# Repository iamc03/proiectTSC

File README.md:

# Proiect TSC
 ## Diagrama Bloc

 ## Bill of Materials
 | Component       | Datasheet       | Link           |
 |-----------------|-----------------|----------------|
 | ESP32-C6-WROOM-1-N8 | - | https://www.snapeda.com/parts/ESP32-C6-WROOM-1-N8/Espressif+Systems/view-part/?ref=eda |
 | CPH3225A | - | https://www.snapeda.com/parts/CPH3225A/Seiko+Instruments/view-part/?ref=eda |
 | DS3231SN# | - | https://www.snapeda.com/parts/DS3231SN%23/Analog+Devices/view-part/?ref=eda |
 | MAX17048G+T10 | - | https://www.snapeda.com/parts/MAX17048G+T10/Analog+Devices/view-part/?ref=eda|
 | MBR0530 | - | https://www.snapeda.com/parts/MBR0530/Onsemi/view-part/?ref=eda |
 | PGB1010603MR | - | https://www.snapeda.com/parts/PGB1010603MR/Littelfuse/view-part/?ref=eda |
 | USBLC6-2SC6Y | - | https://www.snapeda.com/parts/USBLC6-2SC6Y/STMicroelectronics/view-part/?ref=eda |
 | W25Q512JVEIQ | - | https://www.snapeda.com/parts/W25Q512JVEIQ/Winbond+Electronics/view-part/?ref=eda |
 | 640-USB4110-GF-A | - | https://www.mouser.co.uk/ProductDetail/GCT/USB4110-GF-A?qs=KUoIvG%2F9IlYiZvIXQjyJeA%3D%3D |
 | PGB1010603MR | - | https://www.snapeda.com/parts/PGB1010603MR/Littelfuse/view-part/?ref=snap |
 | BUTTONS | - | https://industry.panasonic.com/global/en/products/control/switch/light-touch/number/evqpuj02k |
 | C (1-10) | - | https://componentsearchengine.com/part-view/CC0402MRX5R5BB106/YAGEO |
 | LED | - | https://www.snapeda.com/parts/KP-1608SURCK/Kingbright/view-part/?ref=search&t=LED%200603 |
 | D (1-12) | - | https://www.snapeda.com/parts/PGB1010603MR/Littelfuse/view-part/?ref=eda |
 | R (1-15) | - | https://componentsearchengine.com/part-view/R0402%201%25%20100%20K%20(RC0402FR-07100KL)/YAGEO |
 | Test Pads | - | - |
   
## Funcționalitate hardware
### Alimentare și încărcare
Conector USB + MCP73831: Permite încărcarea unei baterii LiPo prin USB.

LDO (ME6211 sau similar): Reglează tensiunea la 3.3V pentru alimentarea circuitului digital.

Condensatori de decuplare: Plasați strategic pentru stabilizarea alimentării.

### ESP32-C6
Modul WiFi/BLE cu capabilități de conectare și procesare date.

Flash: 4MB / RAM: 512KB.

GPIO multiple folosite pentru comunicații (SPI, I2C) și control periferice.

### E-Ink Display
Controlat prin SPI.

GPIO-uri adiționale pentru semnale de control (busy, reset).

### Protecții
Diodă Schottky (ex: MBR0530) pentru protecție polaritate inversă.

PTC resetabil pentru protecție curent.

### EEPROM / MEMS
EEPROM pentru păstrarea datelor între cicluri de alimentare (presupus U3).

MAX17048 pentru monitorizarea nivelului bateriei (comunicare I2C).

| Pin ESP32-C6 |	Funcție hardware |
|-------------|------------------|
| IO0 |	GPIO / Boot	|
| IO1 |	UART TX |
| IO2 |	UART RX	|
| IO3 |	GPIO	|
| IO4 | GPIO	|
| IO5 |	GPIO	|
| IO6 |	GPIO	|
| IO7 |	GPIO	|
| IO8 |	GPIO	|
| IO9 |	SPI Flash – IO2 |
| IO10 | 	SPI Flash – IO3 |
| IO11 |	SPI Flash – SCK |
| IO12 |	SPI Flash – CS |
| IO13 |	SPI Flash – IO1 |
| IO14 |	SPI Flash – IO0 |
| IO15 |	I2C SDA |
| IO16 |	I2C SCL |
| IO17 |	SPI Display – DC |
| IO18 |	SPI Display – RST |
| IO19 |	SPI Display – CS |
| IO20 |	SPI Display – CLK |
| IO21 |	SPI Display – MOSI |
| IO22 |	SPI Display – BUSY |
| IO23 |	SPI ESD / Qwiic |

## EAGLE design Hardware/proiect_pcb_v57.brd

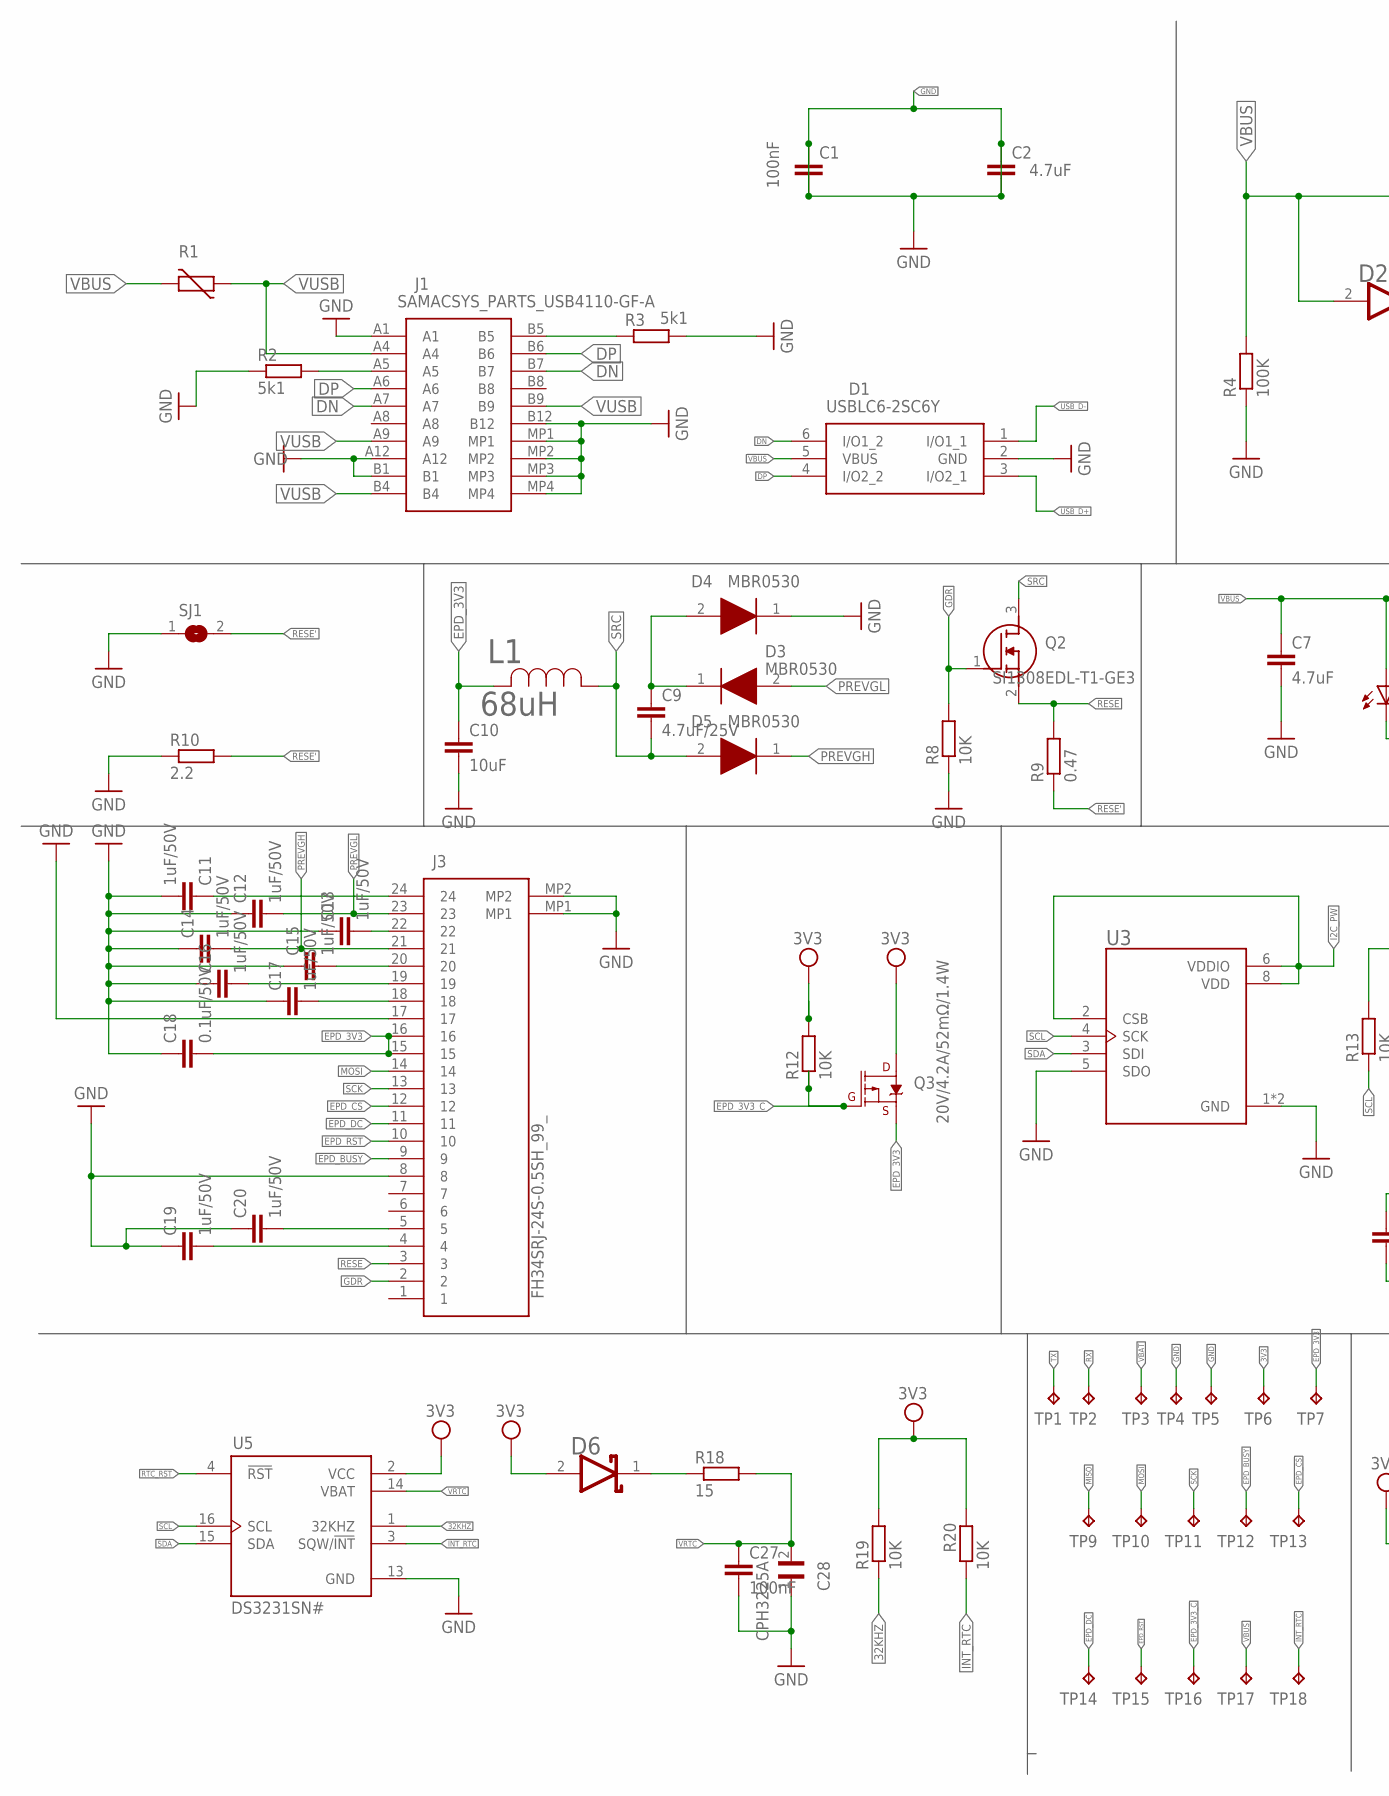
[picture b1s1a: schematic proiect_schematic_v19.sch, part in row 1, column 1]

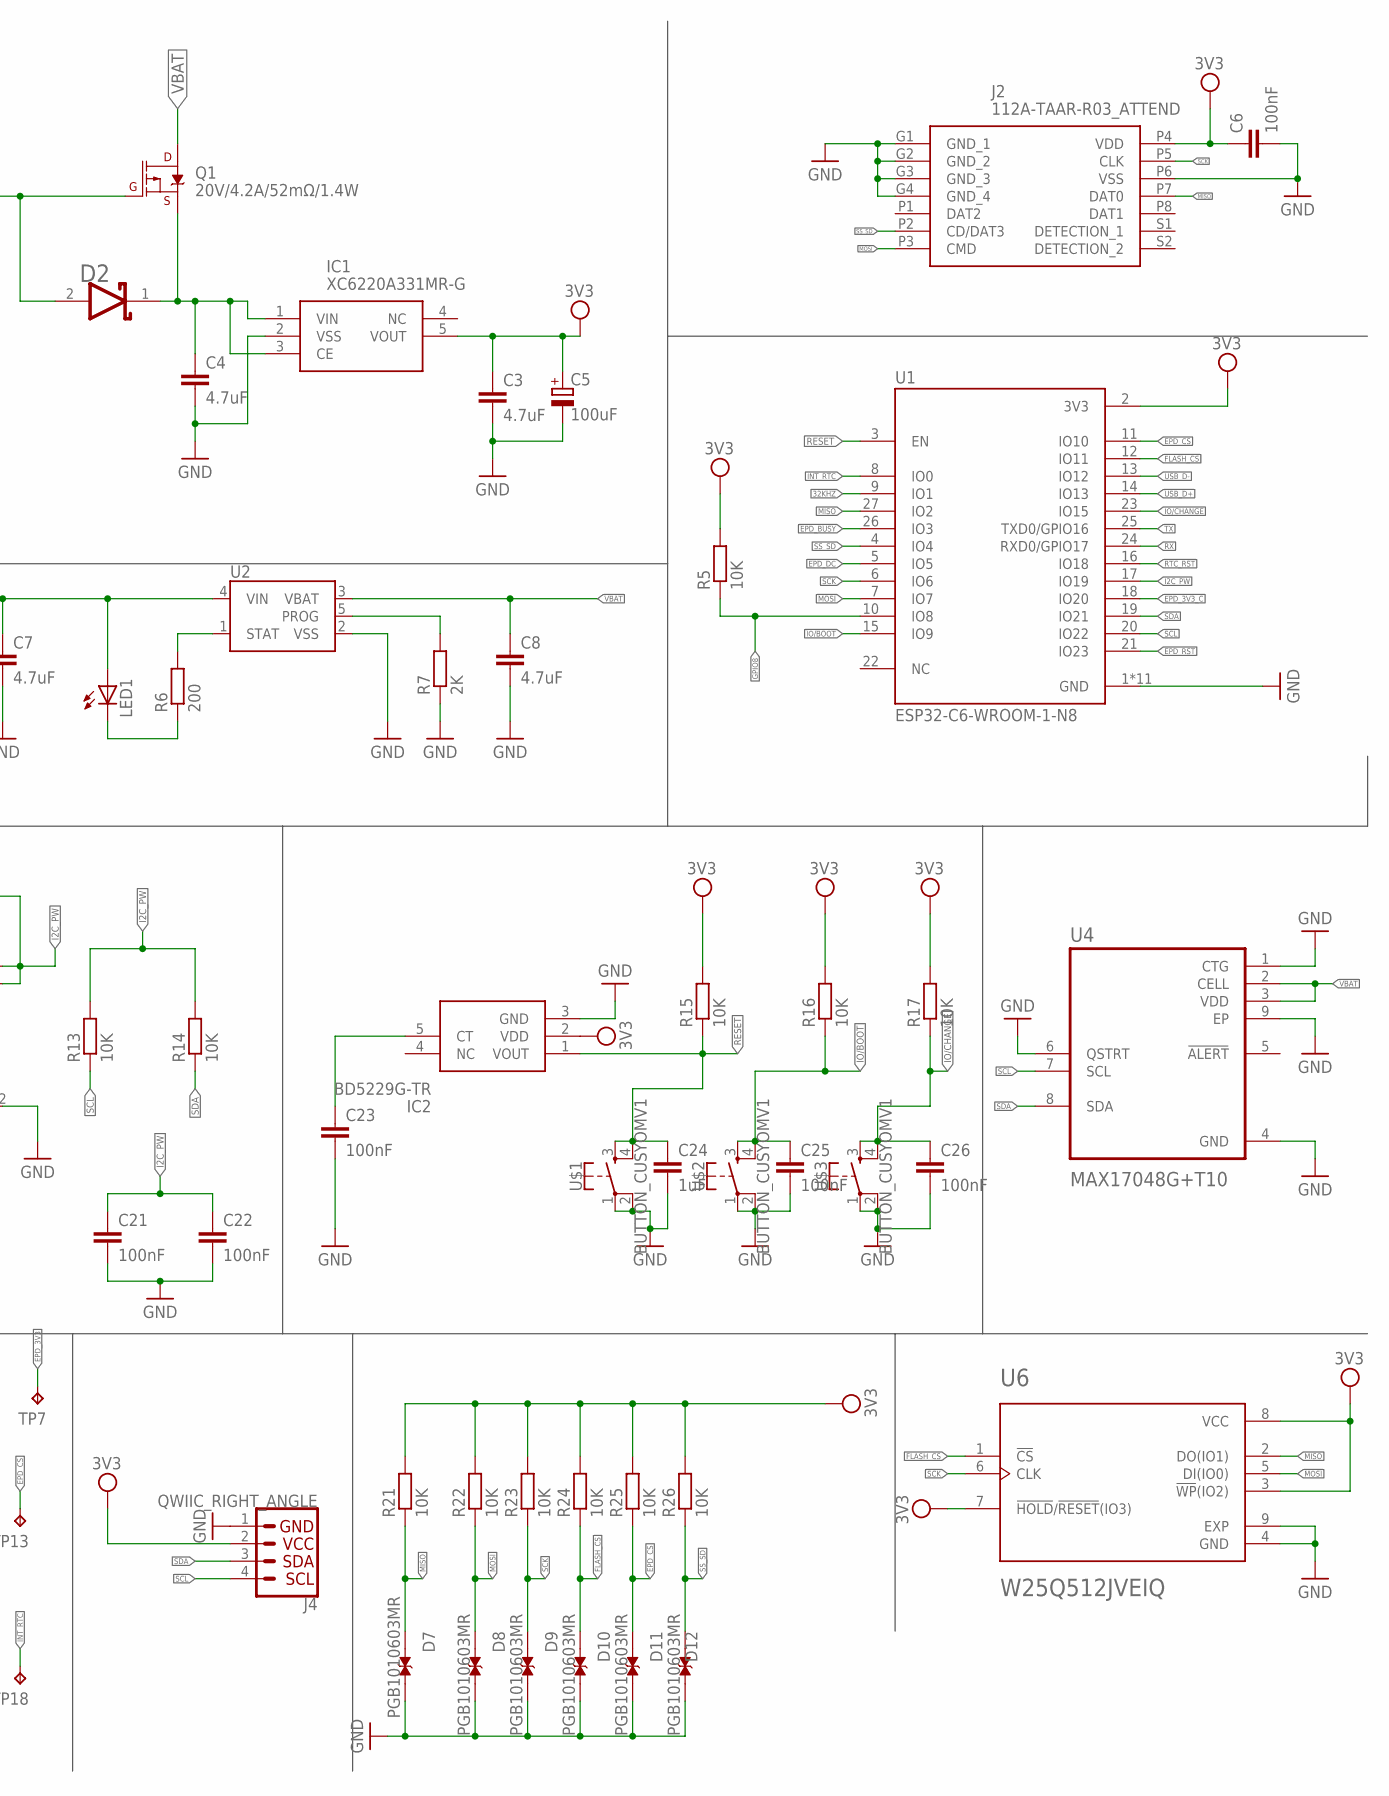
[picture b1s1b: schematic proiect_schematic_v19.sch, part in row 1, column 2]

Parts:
C1, C6, C21, C22, C23, C25, C26, C27: 100nF; ESP32_WROVER_EAGLE-LTSPICE_C0402
C2, C7, C8: 4.7uF; ESP32_WROVER_EAGLE-LTSPICE_C0402
C3, C4: 4.7uF; EAGLE-LTSPICE_C0402
C5: 100uF; RCL_CT3528
C9: 4.7uF/25V; ESP32_WROVER_EAGLE-LTSPICE_C0402
C10: 10uF; ESP32_WROVER_EAGLE-LTSPICE_C0402
C11, C12, C13, C14, C15, C16, C17, C19, C20: 1uF/50V; ESP32_WROVER_EAGLE-LTSPICE_C0402
C18: 0.1uF/50V; ESP32_WROVER_EAGLE-LTSPICE_C0402
C24: 1uF; ESP32_WROVER_EAGLE-LTSPICE_C0402
C28: CPH3225A; CAPCP3225X100N
D1: USBLC6-2SC6Y; SOT95P280X145-6N
D2, D6: ESP32_WROVER_AVX---SD0805S020S1R0_AVX_SD0805S020S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; ESP32_WROVER_AVX---SD0805S020S1R0_AVX_SD0805S020S1R0_0
D3, D4, D5: MBR0530; SOD3716X135N
D7, D8, D9, D10, D11, D12: PGB1010603MR; DIOC1608X36N
IC1: XC6220A331MR-G; SOT95P280X120-5N
IC2: BD5229G-TR; SOT95P280X125-5N
J1: SAMACSYS_PARTS_USB4110-GF-A; SAMACSYS_PARTS_USB4110GFA
J2: 112A-TAAR-R03_ATTEND; 112ATAARR03ATTEND
J3: FH34SRJ-24S-0.5SH_99_; FH34SRJ24S05SH99
J4: QWIIC_RIGHT_ANGLE; JST04_1MM_RA
L1: 68uH; IND_4828-WE-TPC_WRE
LED1: ADAFRUIT_LEDCHIP-LED0603; ADAFRUIT_CHIP-LED0603
Q1, Q3: 20V/4.2A/52mΩ/1.4W; ESP32_WROVER_SPARKFUN-DISCRETESEMI_SOT23-3
Q2: SI1308EDL-T1-GE3; SOT65P210X110-3N
R1: ESP32C6_VARISTORCN1812; ESP32C6_VARISTOR_CT/CN1812
R2, R3: 5k1; ESP32_WROVER_EAGLE-LTSPICE_R0402
R4: 100K; ESP32_WROVER_EAGLE-LTSPICE_R0402
R5, R8, R12, R13, R14, R15, R16, R17, R19, R20, R21, R22, R23, R24, R25, R26: 10K; ESP32_WROVER_EAGLE-LTSPICE_R0402
R6: 200; ESP32_WROVER_EAGLE-LTSPICE_R0402
R7: 2K; ESP32_WROVER_EAGLE-LTSPICE_R0402
R9: 0.47; ESP32_WROVER_EAGLE-LTSPICE_R0402
R10: 2.2; ESP32_WROVER_EAGLE-LTSPICE_R0402
R18: 15; ESP32_WROVER_EAGLE-LTSPICE_R0402
SJ1: SJ
TP1, TP2, TP3, TP4, TP5, TP6, TP7, TP9, TP10, TP11, TP12, TP13, TP14, TP15, TP16, TP17, TP18: TPTP20R; TP20R
U1: ESP32-C6-WROOM-1-N8; XCVR_ESP32-C6-WROOM-1-N8
U2: ESP32_WROVER_SPARKFUN-IC-POWER_MCP73831; ESP32_WROVER_SPARKFUN-IC-POWER_SOT23-5
U3: ESP32_WROVER_BME680_BME680; ESP32_WROVER_BME680_PSON80P300X300X100-8N
U4: MAX17048G+T10; SON50P200X200X80-9N
U5: DS3231SN#; SOIC127P1032X265-16N
U6: W25Q512JVEIQ; SON127P600X800X80-9N
U$1, U$2, U$3: BUTTON_CUSYOMV1; MYBUTTON

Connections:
3V3: C3.1, C5.+, C6.1, D6.2 (ANODE), IC1.5 (VOUT), IC2.2 (VDD), J2.P4 (VDD), J4.2, Q3.3 (D), R5.2, R12.2, R15.2, R16.2, R17.2, R19.2, R20.2, R21.2, R22.2, R23.2, R24.2, R25.2, R26.2, TP6.TP, U1.2 (3V3), U5.2 (VCC), U6.3 (!WP!(IO2)), U6.7 (!HOLD!/!RESET!(IO3)), U6.8 (VCC)
32KHZ: R19.1, U1.9 (IO1), U5.1 (32KHZ)
DN: D1.6 (I/O1_2), J1.A7, J1.B7
DP: D1.4 (I/O2_2), J1.A6, J1.B6
EPD_3V3: C10.1, C18.2, J3.15, J3.16, L1.2, Q3.2 (S), TP7.TP
EPD_3V3_C: Q3.1 (G), R12.1, TP16.TP, U1.18 (IO20)
EPD_BUSY: J3.9, TP12.TP, U1.26 (IO3)
EPD_CS: D11.1, J3.12, R25.1, TP13.TP, U1.11 (IO10)
EPD_DC: J3.11, TP14.TP, U1.5 (IO5)
EPD_RST: J3.10, TP15.TP, U1.21 (IO23)
FLASH_CS: D10.1, R24.1, U1.12 (IO11), U6.1 (!CS)
GDR: J3.2, Q2.1 (G), R8.2
GND: C1.1, C1.2, C2.1, C2.2, C3.2, C4.2, C5.-, C6.2, C7.2, C8.2, C10.2, C11.2, C12.1, C13.1, C14.1, C15.1, C16.1, C17.1, C18.1, C19.1, C20.1, C21.2, C22.2, C23.2, C24.2, C25.2, C26.2, C27.2, C28.1, D1.2 (GND), D4.1 (K), D7.2, D8.2, D9.2, D10.2, D11.2, D12.2, IC1.2 (VSS), IC2.3 (GND), J1.A1, J1.A12, J1.B1, J1.B12, J1.MP1, J1.MP2, J1.MP3, J1.MP4, J2.G1 (GND_1), J2.G2 (GND_2), J2.G3 (GND_3), J2.G4 (GND_4), J2.P6 (VSS), J3.8, J3.17, J3.MP1, J3.MP2, J4.1, R2.1, R3.2, R4.1, R7.1, R8.1, R10.1, SJ1.1, TP4.TP, TP5.TP, U1.1 (GND), U1.28 (GND), U1.29_1 (GND), U1.29_2 (GND), U1.29_3 (GND), U1.29_4 (GND), U1.29_5 (GND), U1.29_6 (GND), U1.29_7 (GND), U1.29_8 (GND), U1.29_9 (GND), U2.2 (VSS), U3.1 (GND), U3.5 (SDO), U3.7 (GND), U4.1 (CTG), U4.4 (GND), U4.6 (QSTRT), U4.9 (EP), U5.13 (GND), U6.4 (GND), U6.9 (EXP), U$1.1, U$1.2, U$2.1, U$2.2, U$3.1, U$3.2
GPIO8: R5.1, U1.10 (IO8)
I2C_PW: C21.1, C22.1, R13.2, R14.2, U1.17 (IO19), U3.2 (CSB), U3.6 (VDDIO), U3.8 (VDD)
INT_RTC: R20.1, TP18.TP, U1.8 (IO0), U5.3 (SQW/!INT)
IO/BOOT: C25.1, R16.1, U1.15 (IO9), U$2.3, U$2.4
IO/CHANGE: C26.1, R17.1, U1.23 (IO15), U$3.3, U$3.4
MISO: D7.1, J2.P7 (DAT0), R21.1, TP9.TP, U1.27 (IO2), U6.2 (DO(IO1))
MOSI: D8.1, J2.P3 (CMD), J3.14, R22.1, TP10.TP, U1.7 (IO7), U6.5 (DI(IO0))
unnamed: J1.A5, R2.2
unnamed: J1.B5, R3.1
unnamed: C11.1, J3.24
unnamed: C4.1, D2.1 (CATHODE), IC1.1 (VIN), IC1.3 (CE), Q1.2 (S)
unnamed: R6.2, U2.1 (STAT)
unnamed: LED1.C, R6.1
unnamed: R7.2, U2.5 (PROG)
unnamed: C9.1, D3.1 (K), D4.2 (A)
unnamed: C13.2, J3.22
unnamed: C15.2, J3.20
unnamed: C16.2, J3.19
unnamed: C17.2, J3.18
unnamed: C19.2, J3.4
unnamed: C20.2, J3.5
unnamed: C23.1, IC2.5 (CT)
unnamed: D6.1 (CATHODE), R18.1
PREVGH: C14.2, D5.1 (K), J3.21
PREVGL: C12.2, D3.2 (A), J3.23
RESE: J3.3, Q2.2 (S), R9.2
RESE': R9.1, R10.2, SJ1.2
RESET: C24.1, IC2.1 (VOUT), R15.1, U1.3 (EN), U$1.3, U$1.4
RTC_RST: U1.16 (IO18), U5.4 (!RST)
RX: TP2.TP, U1.24 (RXD0/GPIO17)
SCK: D9.1, J2.P5 (CLK), J3.13, R23.1, TP11.TP, U1.6 (IO6), U6.6 (CLK)
SCL: J4.4, R13.1, U1.20 (IO22), U3.4 (SCK), U4.7 (SCL), U5.16 (SCL)
SDA: J4.3, R14.1, U1.19 (IO21), U3.3 (SDI), U4.8 (SDA), U5.15 (SDA)
SRC: C9.2, D5.2 (A), L1.1, Q2.3 (D)
SS_SD: D12.1, J2.P2 (CD/DAT3), R26.1, U1.4 (IO4)
TX: TP1.TP, U1.25 (TXD0/GPIO16)
USB_D+: D1.3 (I/O2_1), U1.14 (IO13)
USB_D-: D1.1 (I/O1_1), U1.13 (IO12)
VBAT: C8.1, Q1.3 (D), TP3.TP, U2.3 (VBAT), U4.2 (CELL), U4.3 (VDD)
VBUS: C7.1, D1.5 (VBUS), D2.2 (ANODE), LED1.A, Q1.1 (G), R1.2, R4.2, TP17.TP, U2.4 (VIN)
VRTC: C27.1, C28.2, R18.2, U5.14 (VBAT)
VUSB: J1.A4, J1.A9, J1.B4, J1.B9, R1.1

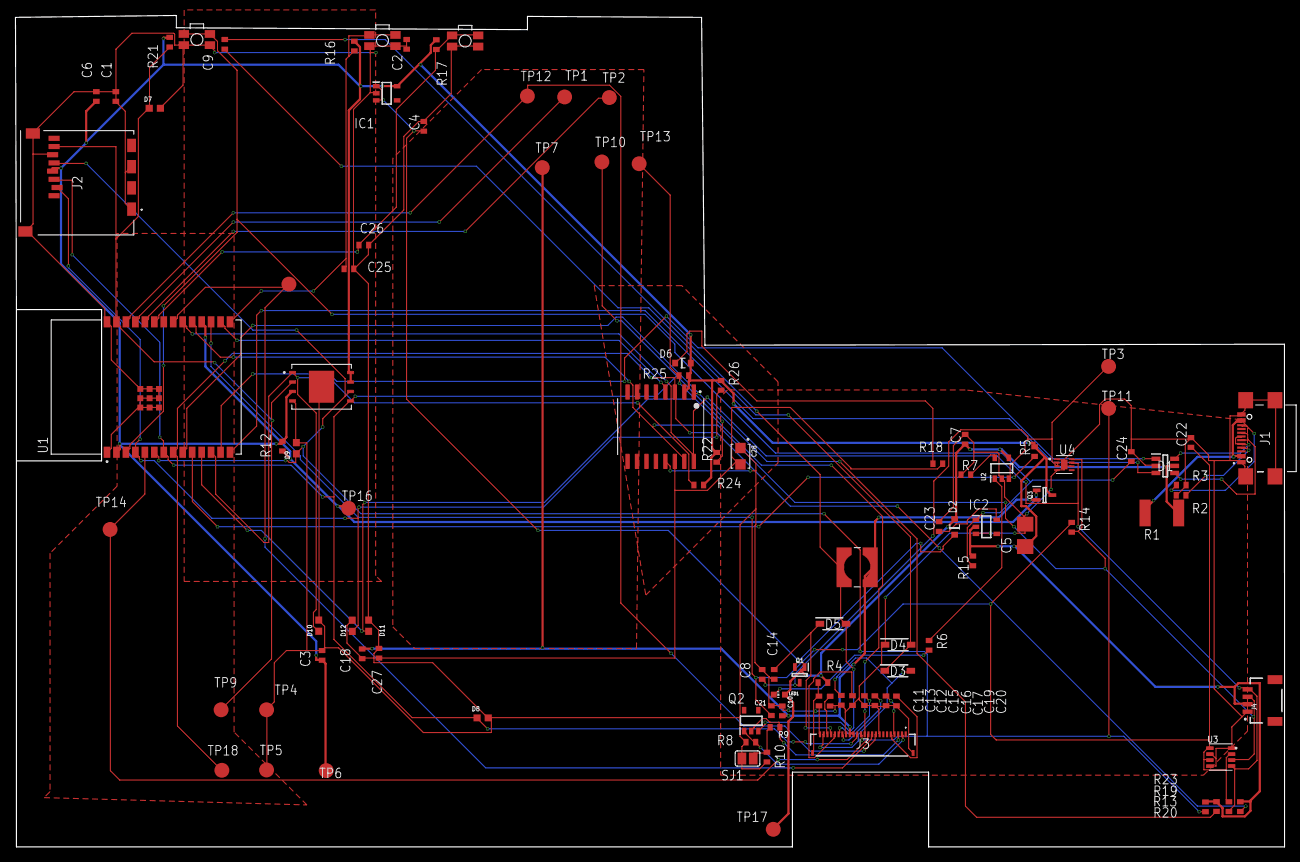
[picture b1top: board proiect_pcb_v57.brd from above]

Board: 2 copper layers, 170.3 x 111.6 mm, 103 parts (0 on the bottom side), 55 nets.

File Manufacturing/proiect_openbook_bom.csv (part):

Qty,Value,Device,Package,Parts,Description,ARROW_PART_NUMBER,ARROW_PRICE-STOCK,AVAILABILITY,CENTROID_NOT_SPECIFIED,CHECK_PRICES,COPYRIGHT,DATASHEET,DESCRIPTION,DIGIKEY_DESCRIPTION,DIGIKEY_PART_NUMBER,HEIGHT,LEAD_FREE,MANUFACTURER_NAME,MANUFACTURER_PART_NUMBER,MF,MFR_NAME,MOUSER_PART_NUMBER,MOUSER_PRICE-STOCK,MOUSER_TESTING_PART_NUMBER,MOUSER_TESTING_PRICE-STOCK,MP,MPN,PACKAGE,POPULARITY,PREFIX,PRICE,PROD_ID,PURCHASE-URL,ROHS,SNAPEDA_LINK,SPICEMODEL,SPICEPREFIX,TEMPERATURE_RANGE_HIGH,TEMPERATURE_RANGE_LOW,TP_SIGNAL_NAME,VALUE
1,,ADAFRUIT_LEDCHIP-LED0603,ADAFRUIT_CHIP-LED0603,LED1,LED,,,,,,,,,,,,,,,,,,,,,,,,,,,,,,,,,,,,
1,,SJ,SJ,SJ1,"SMD solder JUMPER",,,,,,,,,,,,,,,,,,,,,,,,3,,,,,,,,,,,,
1,0.1uF/50V,ESP32_WROVER_EAGLE-LTSPICE_CC0402,ESP32_WROVER_EAGLE-LTSPICE_C0402,C18,"CAPACITOR, European symbol",,,,,,,,,,,,,,,,,,,,,,,,,,,,,,,NONE,C,,,,
1,0.47,ESP32_WROVER_EAGLE-LTSPICE_RR0402,ESP32_WROVER_EAGLE-LTSPICE_R0402,R9,"RESISTOR, European symbol",,,,,,,,,,,,,,,,,,,,,,,,,,,,,,,NONE,R,,,,
1,100K,ESP32_WROVER_EAGLE-LTSPICE_RR0402,ESP32_WROVER_EAGLE-LTSPICE_R0402,R4,"RESISTOR, European symbol",,,,,,,,,,,,,,,,,,,,,,,,,,,,,,,NONE,R,,,,
8,100nF,ESP32_WROVER_EAGLE-LTSPICE_CC0402,ESP32_WROVER_EAGLE-LTSPICE_C0402,"C1, C6, C21, C22, C23, C25, C26, C27","CAPACITOR, European symbol",,,,,,,,,,,,,,,,,,,,,,,,,,,,,,,NONE,C,,,,
1,100uF,RCL_CPOL-EUCT3528,RCL_CT3528,C5,"POLARIZED CAPACITOR, European symbol",,,,,,,,,,,,,,,,,,,,,,,,0,,,,,,,,C,,,,
16,10K,ESP32_WROVER_EAGLE-LTSPICE_RR0402,ESP32_WROVER_EAGLE-LTSPICE_R0402,"R5, R8, R12, R13, R14, R15, R16, R17, R19, R20, R21, R22, R23, R24, R25, R26","RESISTOR, European symbol",,,,,,,,,,,,,,,,,,,,,,,,,,,,,,,NONE,R,,,,
1,10uF,ESP32_WROVER_EAGLE-LTSPICE_CC0402,ESP32_WROVER_EAGLE-LTSPICE_C0402,C10,"CAPACITOR, European symbol",,,,,,,,,,,,,,,,,,,,,,,,,,,,,,,NONE,C,,,,
1,112A-TAAR-R03_ATTEND,112A-TAAR-R03_ATTEND,112ATAARR03ATTEND,J2,"Micro SD Card Socket, Push-Push Type, Top Mount, SMT, H=1.83mm, 10u",,,,,,,,"Micro SD Card Socket"," Push-Push Type"," Top Mount"," SMT"," H=1.83mm"," 10u",,,1.9mm,,ATTEND,"112A-TAAR-R03 ATTEND",,,,,,,,,,,,,,,,,
1,15,ESP32_WROVER_EAGLE-LTSPICE_RR0402,ESP32_WROVER_EAGLE-LTSPICE_R0402,R18,"RESISTOR, European symbol",,,,,,,,,,,,,,,,,,,,,,,,,,,,,,,NONE,R,,,,
1,1uF,ESP32_WROVER_EAGLE-LTSPICE_CC0402,ESP32_WROVER_EAGLE-LTSPICE_C0402,C24,"CAPACITOR, European symbol",,,,,,,,,,,,,,,,,,,,,,,,,,,,,,,NONE,C,,,,
9,1uF/50V,ESP32_WROVER_EAGLE-LTSPICE_CC0402,ESP32_WROVER_EAGLE-LTSPICE_C0402,"C11, C12, C13, C14, C15, C16, C17, C19, C20","CAPACITOR, European symbol",,,,,,,,,,,,,,,,,,,,,,,,,,,,,,,NONE,C,,,,
1,2.2,ESP32_WROVER_EAGLE-LTSPICE_RR0402,ESP32_WROVER_EAGLE-LTSPICE_R0402,R10,"RESISTOR, European symbol",,,,,,,,,,,,,,,,,,,,,,,,,,,,,,,NONE,R,,,,
1,200,ESP32_WROVER_EAGLE-LTSPICE_RR0402,ESP32_WROVER_EAGLE-LTSPICE_R0402,R6,"RESISTOR, European symbol",,,,,,,,,,,,,,,,,,,,,,,,,,,,,,,NONE,R,,,,
2,20V/4.2A/52mO/1.4W,ESP32_WROVER_SPARKFUN-DISCRETESEMI_MOSFET_PCH-DMG2305UX-7,ESP32_WROVER_SPARKFUN-DISCRETESEMI_SOT23-3,"Q1, Q3","P-channel MOSFETs",,,,,,,,,,,,,,,,,,,,,,,,,,,TRAN-14388,,,,,,,,,20V/4.2A/52mO/1.4W
1,2K,ESP32_WROVER_EAGLE-LTSPICE_RR0402,ESP32_WROVER_EAGLE-LTSPICE_R0402,R7,"RESISTOR, European symbol",,,,,,,,,,,,,,,,,,,,,,,,,,,,,,,NONE,R,,,,
2,4.7uF,EAGLE-LTSPICE_CC0402,EAGLE-LTSPICE_C0402,"C3, C4","CAPACITOR, European symbol",,,,,,,,,,,,,,,,,,,,,,,,,,,,,,,NONE,C,,,,
3,4.7uF,ESP32_WROVER_EAGLE-LTSPICE_CC0402,ESP32_WROVER_EAGLE-LTSPICE_C0402,"C2, C7, C8","CAPACITOR, European symbol",,,,,,,,,,,,,,,,,,,,,,,,,,,,,,,NONE,C,,,,
1,4.7uF/25V,ESP32_WROVER_EAGLE-LTSPICE_CC0402,ESP32_WROVER_EAGLE-LTSPICE_C0402,C9,"CAPACITOR, European symbol",,,,,,,,,,,,,,,,,,,,,,,,,,,,,,,NONE,C,,,,
2,5k1,ESP32_WROVER_EAGLE-LTSPICE_RR0402,ESP32_WROVER_EAGLE-LTSPICE_R0402,"R2, R3","RESISTOR, European symbol",,,,,,,,,,,,,,,,,,,,,,,,,,,,,,,NONE,R,,,,
1,68uH,744043680IND_4828-WE-TPC_WRE,IND_4828-WE-TPC_WRE,L1,,,,,,,"Copyright (C) 2024 Ultra Librarian. All rights reserved.",,,,,,,,744043680,,"Wurth Electronics",,,,,,,,,,,,,,,,,,,,
1,BD5229G-TR,BD5229G-TR,SOT95P280X125-5N,IC2,"Voltage Detector with Adjustable Delay Time: CMOS processes are utilized to develop high precision, low current consumption CMOS reset ICs that allow arbitrary setting of the delay time. The extensive lineup includes both Nch Open Drain and CMOS output types in a wide range of detection voltages (from 2.3V to 6.0V, in 0.1V steps), enabling selection of the ideal solution based on customer requirements. In addition, the entire series is of course both lead-free and RoHS-compliant.",,,,,,,,"Voltage Detector with Adjustable Delay Time: CMOS processes are utilized to develop high precision"," low current consumption CMOS reset ICs that allow arbitrary setting of the delay time. The extensive lineup includes both Nch Open Drain and CMOS output types in a wide range of detection voltages (from 2.3V to 6.0V"," in 0.1V steps)"," enabling selection of the ideal solution based on customer requirements. In addition"," the entire series is of course both lead-free and RoHS-compliant.",,,1.25mm,,"ROHM Semiconductor",BD5229G-TR,,,755-BD5229G-TR,https://www.mouser.co.uk/ProductDetail/ROHM-Semiconductor/BD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,,,,,,,,,,,,,,
3,BUTTON_CUSYOMV1,BUTTON_CUSYOMV1,MYBUTTON,"U$1, U$2, U$3",,,,,,,,,,,,,,,,,,,,,,,,,,,,,,,,,,,,,
1,CPH3225A,CPH3225A,CAPCP3225X100N,C28,"Cap 0.011F 3.3V 1210 Flat Check availability",,,"Not in stock",,https://www.snapeda.com/parts/CPH3225A/Seiko+Instruments/vie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,,," 11 mF (EDLC) Supercapacitor 3.3 V 1210 (3225 Metric) - - ",,,,,,,"Seiko Instruments",,,,,,CPH3225A,,"1210 Seiko",,,None,,"https://www.snapeda.com/api/url_track_click_mouser/?unipart_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 Instruments&part_name=CPH3225A&search_term=None",,https://www.snapeda.com/parts/CPH3225A/Seiko+Instruments/vie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,,,,,,
1,DS3231SN#,DS3231SN#,SOIC127P1032X265-16N,U5,"Real Time Clock Serial 16-Pin SOIC W T/R     Check availability",,,"In Stock",,https://www.snapeda.com/parts/DS3231SN%23/Analog+Devices/vie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,,," Extremely Accurate I²C-Integrated RTC/TCXO/Crystal ",,,,,,,"Analog Devices",,,,,,DS3231SN#,,"SOIC-16 Maxim",,,None,,"https://www.snapeda.com/api/url_track_click_mouser/?unipart_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 Devices&part_name=DS3231SN#&search_term=None",,https://www.snapeda.com/parts/DS3231SN%23/Analog+Devices/vie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,,,,,,
1,ESP32-C6-WROOM-1-N8,ESP32-C6-WROOM-1-N8,XCVR_ESP32-C6-WROOM-1-N8,U1,"Check availability",,,"In Stock",,https://www.snapeda.com/parts/ESP32-C6-WROOM-1-N8/Espressif+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,,," Multiprotocol Modules ESP32-C6 module"," Wi-Fi 6 in 2.4 GHz band"," Bluetooth 5"," Zigbee 3.0 and Thread. ESP34-WROOM Compatible - ENGINEERING SAMPLE ",,,,,,,"Espressif Systems",,,,,,ESP32-C6-WROOM-1-N8,,None,,,None,,,,https://www.snapeda.com/parts/ESP32-C6-WROOM-1-N8/Espressif+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,,,
1,ESP32C6_VARISTORCN1812,ESP32C6_VARISTORCN1812,ESP32C6_VARISTOR_CT/CN1812,R1,VARISTOR,,,,,,,,,,,,,,,,,,,,,,,,0,,,,,,,,,,,,
2,ESP32_WROVER_AVX---SD0805S020S1R0_AVX_SD0805S020S1R0_0_0AVX_SD0805S020S1R0_0_0,ESP32_WROVER_AVX---SD0805S020S1R0_AVX_SD0805S020S1R0_0_0AVX_SD0805S020S1R0_0_0,ESP32_WROVER_AVX---SD0805S020S1R0_AVX_SD0805S020S1R0_0,"D2, D6","Schottky Barrier Rectifier Diode",,,,No,,,http://datasheets.avx.com/schottky.pdf,,"DIODE SCHOTTKY 20V 1A 0805",478-7800-1-ND,,yes,,,AVX,,581-SD0805S020S1R0,,,,,,"0805 (2012 metric)",,D,,,,yes,,,,+125°C,-55°C,,
1,ESP32_WROVER_BME680_BME680,ESP32_WROVER_BME680_BME680,ESP32_WROVER_BME680_PSON80P300X300X100-8N,U3,"Integrated Environmental Unit",,,Unavailable,,,,," Integrated Environmental Unit ",,,,,,,"Bosch Sensortec",,,,,,BME680,,"LGA-8 Bosch Tools",,,None,,,,,,,,,,
1,ESP32_WROVER_SPARKFUN-IC-POWER_MCP73831,ESP32_WROVER_SPARKFUN-IC-POWER_MCP73831,ESP32_WROVER_SPARKFUN-IC-POWER_SOT23-5,U2,"MCP73831T Li-Ion, Li-Pol Controller",,,,,,,,,,,,,,,,,,,,,,,,,,,IC-09995,,,,,,,,,
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
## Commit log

2025-04-06 Create LICENSE
2025-04-06 Create placeholder
2025-04-12 Fix: Removed valori din silkscreen, issue #4
2025-04-12 Rezolvat valori silkscreen, closes #4
2025-04-12 Rezolvat right angles trasee, closes #3
2025-04-13 Rezolvat erori DRC, closes #2
2025-04-13 Delete Hardware/proiect_pcb_v24.brd
    Old version
2025-04-13 Delete Hardware/proiect_pcb v26.brd
    Old version
2025-04-13 Delete Hardware/proiect_pcb v22.brd
    Old version
2025-04-13 Rezolvat lipsa componente 3D, closes #5
2025-04-13 Delete Mechanical/OpenBook (design complet) v1.f3z
    Old version
2025-04-13 Delete Mechanical/OpenBook(exploded) v1.zip
    Old version
2025-04-13 BOM complete in README

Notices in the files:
parts and their libraries:
COPYRIGHT: Copyright (C) 2024 Ultra Librarian. All rights reserved.
